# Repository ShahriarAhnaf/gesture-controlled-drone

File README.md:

# PalmPilot

Fly a drone with your hands. Two glove controllers, each an ESP32-S3 with five
flex sensors and a motion sensor, send their readings over Bluetooth to a third
ESP32-S3, the hub. The hub turns finger curl and hand tilt into stick commands for
ArduCopter. The controller is real hardware; the drone is simulated and flies on
screen.

## How it works

```text
left glove  ─┐
             ├─ BLE ─> hub ─ USB ─> laptop ─> ArduCopter ─> motor outputs ─> physics ─> 3D view
right glove ─┘          one command every 20 ms
```

The drone on screen moves only because ArduCopter's motor outputs moved it. No
gesture moves the drone directly.

On the laptop, ArduCopter runs as ArduPilot's native simulator (SITL) in real time.
The same firmware can also run on an emulated STM32F405 flight controller in the
[Simantic](https://simantic.com) simulator, which is how the automated tests fly it.

## Gestures

| Hand | Movement | Drone |
|---|---|---|
| Left | curl four fingers | throttle: open is zero, half curl holds height |
| Left | roll the hand | yaw |
| Right | tilt forward or back | pitch |
| Right | tilt left or right | roll |
| Left | press the button | ENABLE: commands only count while enabled |

Full table, deadbands and safety interlocks: [docs/gesture-mapping.md](docs/gesture-mapping.md).

## Hardware

Three ESP32-S3 DevKits, ten flex sensors and two Adafruit LSM6DS3TR-C + LIS3MDL
motion breakouts, on breadboards for now.

The [Rev B PCB design](hardware/README.md) replaces the DevKits with directly
soldered ESP32-S3-WROOM-1 modules on both hands and the hub. It includes KiCad
schematics, four-layer routing, fabrication review exports, passive simulation
evidence and Blender hand renders. The PCB revision still needs bench
qualification; the breadboard results above do not validate the new boards.

Parts: [docs/bom.md](docs/bom.md). Wiring for each board: [docs/wiring/](docs/wiring/README.md).

## Status

- The whole system works in simulation, from the gloves' firmware to the flying
  drone: both hands and the hub run their real firmware on simulated ESP32-S3s and
  fly ArduCopter on an emulated F405. The latest test run passed 321 of 322 checks.
- The physical controller is built on breadboards and has flown the simulated
  drone. One problem is open: a hand sometimes stops sending while it stays
  connected. Notes: [docs/bench-bringup.md](docs/bench-bringup.md).
- Not done yet: the physical test procedures, a soldered build, and pairing.

## Try it

Build the firmware (ESP-IDF v5.5.2):

```sh
idf.py -C firmware/apps/hand -D SDKCONFIG_DEFAULTS="sdkconfig.defaults;sdkconfig.left" build
idf.py -C firmware/apps/hub build
```

Fly the simulated drone with the keyboard, or with a physical hub (needs an
ArduPilot SITL build of Copter-4.7.1 in `tmp/ardupilot` and pymavlink):

```sh
python simulation/drone/demo_view.py --manual             # then open http://localhost:8765
python simulation/drone/demo_view.py --hub /dev/cu.usbserial-XXXX
```

The automated simulation tests (`firmware/tests/`) need the Simantic engine and
board files that are not public yet; [firmware/README.md](firmware/README.md)
describes them.

## How it was tested

Every feature was written and tested in simulation before any sensor was wired.
The simulator runs the exact images that are flashed onto the boards, with test
inputs entering through the simulated chip's own ADC, I2C and GPIO. The same images
then went onto the physical boards.

- [docs/simulation.md](docs/simulation.md): how the simulation runs, the tests, and how the physics was checked
- [docs/test-plan.md](docs/test-plan.md): every test, in order
- [docs/bench-bringup.md](docs/bench-bringup.md): moving to the physical boards, and what simulation could not catch
- [docs/demo.md](docs/demo.md): the laptop demo

## Repository layout

```text
firmware/apps/          hand and hub firmware (and a scripted stand-in hand for tests)
firmware/components/    logic shared by hand and hub: gesture mapping, interlocks, packet format
firmware/tests/         simulation test suites; run_all.sh runs them all
firmware/tools/         build and simulation wrappers; bench/ has tools for the physical boards
simulation/drone/       the bridge to ArduCopter, the physics model, the 3D view
docs/                   design, wiring, tests and notes
hardware/               Rev B module PCBs, electrical evidence and Blender assembly
```

Contributing: [CONTRIBUTING.md](CONTRIBUTING.md).

## Licence

MIT ([LICENSE](LICENSE)). `simulation/drone/ardupilot_frame.py` is a port of
ArduPilot code and is GPLv3; [NOTICE](NOTICE) lists it and the other exceptions.

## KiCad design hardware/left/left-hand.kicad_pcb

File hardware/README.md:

# PalmPilot Rev B — direct ESP32-S3-WROOM module boards

18 November 2026. Replaces the Rev A DevKit carriers at the canonical LEFT,
RIGHT and HUB KiCad paths. Rev A remains in git commit
`d93c8d5c258abfb121f0f205c3fb2d9bdec95d6e`. Rev B is an engineering
review on `hardware/wroom-module-revb`; no boards were ordered.

All three boards are **50 × 58 mm, four copper layers, 1.6 mm nominal**. Each
contains one **ESP32-S3-WROOM-1-N16R8 soldered directly to the PCB**, using its
built-in PCB antenna. There are no DevKit boards or module socket rows.
The 18 × 25.5 mm module overhangs the front edge by 6.25 mm. Its native keepout
contains no host copper. LEFT/RIGHT each retain five flex inputs and an external
Adafruit #5543 motion board. HUB includes its GPIO7 CALIBRATE circuit.

## Integrated support circuit

- TLV1117LV33DCYR ceramic-stable 1 A LDO converts USB 5 V to 3.3 V.
  22 uF / 25 V / X5R 1206 capacitors serve input, output and module bulk;
  local 100 nF capacitors bypass the module and bridge.
- CH340C operates at 3.3 V, with V3 tied to VCC and its internal oscillator.
  ESP GPIO43/TXD0 connects to bridge RXD; bridge TXD connects to GPIO44/RXD0.
  The hub retains UART0 / 115200 baud / JSON USB-to-laptop communication.
  Its R232 mode input is intentionally NC, using the manufacturer's internal pull-down.
- USB Micro-B J1 supplies power and programming/data; USBLC6-2SC6 protects D+/D−.
  The shield is grounded. Native ESP USB GPIO19/20 remain NC.
- EN uses 10 kR / 1 uF and RESET SW1. GPIO0 uses 10 kR and BOOT SW2.
  Hold BOOT, tap RESET, release BOOT to enter the ROM downloader.
  This revision uses manual flashing controls; it has no DTR/RTS auto-reset.
- No battery input or charger is fitted. Each hand uses a USB supply; HUB uses
  a USB data cable to the host. BLE connects the hands to the hub.

## Preserved interfaces and firmware

| Connector | Role | Pins |
|---|---|---|
| J4/J5/J6/J7/J8 | Thumb/index/middle/ring/little flex | 1 = 3V3, 2 = ADC; GPIO1/2/4/5/6 |
| J2, hands only | External #5543 motion harness | 1 GND, 2 3V3, 3 SDA/GPIO8, 4 SCL/GPIO9 |
| J9, LEFT only | Normally-open ENABLE switch | 1 switch, 2 GND; GPIO7 conditioning |
| SW3, HUB only | CALIBRATE | GPIO7 through 10 kR / 100 nF / 1 kR network |

The PH-4 harness is not a QT-compatible cable; verify its mapping. Each flex
input retains 47 kR 1% / 100 nF to ground. The breakout supplies I2C pull-ups;
none are added here. GPIO10, GPIO3/45/46 strapping pins, unused native USB and
module GPIO35/36/37 associated with octal PSRAM remain NC. RIGHT GPIO7 is NC.
The upstream firmware was not modified or rebuilt in this revision. Its existing
8 MB flash image fits the selected 16 MB flash module; PSRAM remains disabled.
A physical boot/flash/USB/BLE/ADC/IMU test is still required, including module
variant and firmware configuration. HUB bench mode disables CALIBRATE.

## Checks and limits

All three saved projects pass KiCad 10.0.3 ERC, DRC with schematic parity, and a
read-only native pad-connectivity audit: **zero reported violations or opens**.
Tracks follow H/V/45 geometry. Reports, board hashes, BOMs, four-layer Gerbers,
drills, layer plots, schematic PDFs and component-bearing GLBs are in `build/`.
All twelve copper Gerber layers were also rendered with PyGerber 2.4.3 at
500 dpi and visually inspected; In1 remains a continuous reference plane.
The project-local WROOM footprint retains the native land pattern, thermal vias,
RF keepout and STEP model; only off-board silkscreen was removed.

In1.Cu is a continuous ground reference; In2.Cu carries 3V3 and a few slow signals
and the USB 5 V feed. Top and bottom have ground pours and stitching. Exact
fabricator stackup, USB differential impedance and signal quality are **not
qualified**. The short full-speed USB route includes a crossover via pair on D+
with nearby return stitching; it is not a length-matched or impedance-certified
USB release. Confirm the Molex connector mechanical drawing and mating clearance
before manufacture; its exact installed-library 3D model is unavailable.

[Simulation results](simulation/REPORT.md) bind to the actual new netlists.
Passive response, EN timing and assumed rail impedance were simulated; the LDO
control loop, radio current waveform, antenna/body interaction, sensor silicon
and raw ADC transfer were not. At 5.25 V / 0.5 A the LDO dissipates about 0.975 W:
actual sustained-load and worn temperatures must be measured. I2C capacitance
and firmware raw fault thresholds remain bench qualifications.

BOMs contain selected module, active-component and capacitor MPNs. Resistor,
connector and switch procurement variants are not frozen; BOMs and Gerbers are
engineering review outputs, not an assembly order or fabrication release.

## Render and rebuilding

`render/palmpilot-two-hands.blend` contains both licensed real hand meshes, the
actual three module-board GLBs, ten sensor films and an illustrative harness.
`render/module-on-hand.png` shows the left module closely;
`render/right-hand-detail.png` and `render/hub-detail.png` show the other two. There is no added
DevKit or module proxy. The missing USB connector shell, external IMU envelopes,
straps, cushions, screws, sensor films and cables are illustrative; this does not
establish wearable fit. See [render notes](render/README.md).

Use KiCad's bundled Python for `scripts/generate.py`, then `scripts/export.py`,
`scripts/audit.py` and `simulation/run.py`. Use Blender for `render/scene.py` after
exporting all three GLBs; `render/details.py` adds the right-hand and hub close-ups.
Native GUI initialization may need an unsandboxed macOS
process. Export fails closed on ERC/DRC violations.

## Manufacturer references

- [Espressif module datasheet](https://www.espressif.com/sites/default/files/documentation/esp32-s3-wroom-1_wroom-1u_datasheet_en.pdf)
- [Espressif schematic checklist](https://docs.espressif.com/projects/esp-hardware-design-guidelines/en/latest/esp32s3/schematic-checklist.html)
- [Espressif layout guidance](https://docs.espressif.com/projects/esp-hardware-design-guidelines/en/latest/esp32s3/pcb-layout-design.html)
- [TI TLV1117LV](https://www.ti.com/lit/ds/symlink/tlv1117lv.pdf)
- [WCH CH340 manual](https://www.wch-ic.com/downloads/CH340DS1_PDF.html)
- [ST USBLC6-2](https://www.st.com/resource/en/datasheet/usblc6-2.pdf)
- [Molex USB connector](https://www.molex.com/en-us/products/part-detail/1050170001)

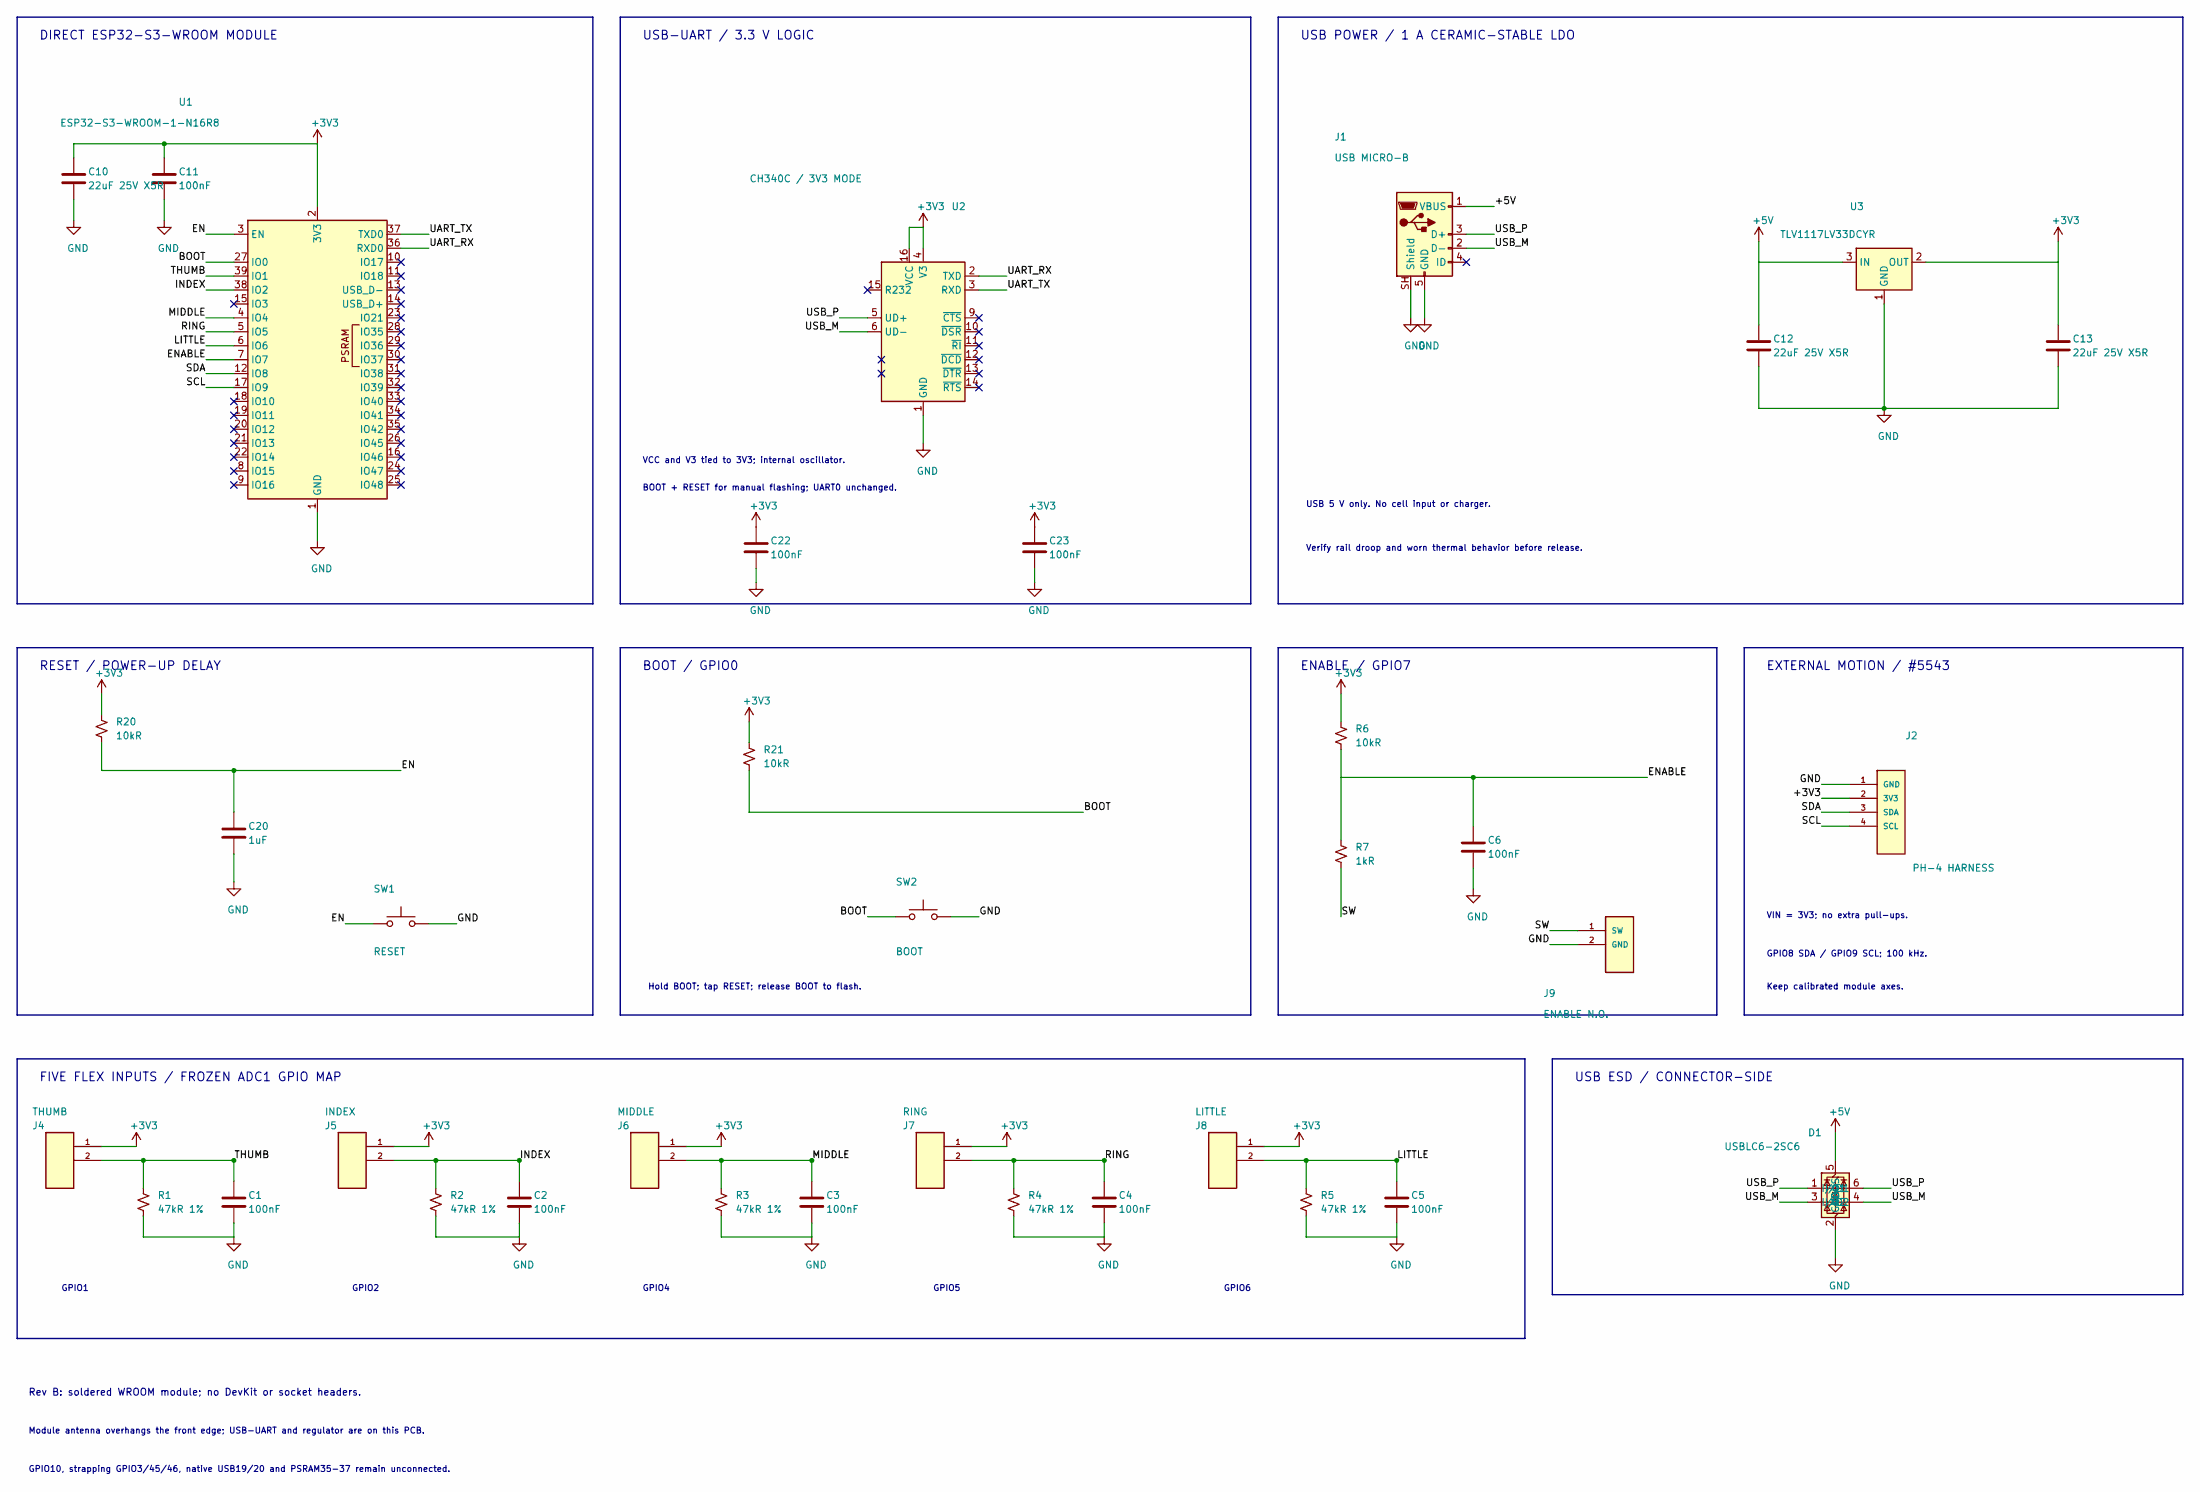
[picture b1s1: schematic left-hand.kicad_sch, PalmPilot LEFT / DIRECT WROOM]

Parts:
C1, C2, C3, C4, C5, C6, C11, C22, C23: 100nF; C_0805_2012Metric; MPN CC0805KRX7R9BB104; LCSC C49678
C10, C12, C13: 22uF 25V X5R; C_1206_3216Metric; MPN CL31A226KAHNNNE; LCSC C12891
C20: 1uF; C_0805_2012Metric; MPN CL21B105KBFNNNE; LCSC C28323
D1: USBLC6-2SC6; SOT-23-6; MPN USBLC6-2SC6; LCSC C7519
J1: USB MICRO-B; USB_Micro-B_Molex-105017-0001; MPN 1050170001; LCSC C136000
J2: PH-4 HARNESS; JST_PH_B4B-PH-K_1x04_P2.00mm_Vertical
J4: THUMB; JST_PH_B2B-PH-K_1x02_P2.00mm_Vertical
J5: INDEX; JST_PH_B2B-PH-K_1x02_P2.00mm_Vertical
J6: MIDDLE; JST_PH_B2B-PH-K_1x02_P2.00mm_Vertical
J7: RING; JST_PH_B2B-PH-K_1x02_P2.00mm_Vertical
J8: LITTLE; JST_PH_B2B-PH-K_1x02_P2.00mm_Vertical
J9: ENABLE N.O.; JST_PH_B2B-PH-K_1x02_P2.00mm_Vertical
R1, R2, R3, R4, R5: 47kR 1%; R_0805_2012Metric
R6, R20, R21: 10kR; R_0805_2012Metric
R7: 1kR; R_0805_2012Metric
SW1: RESET; SW_PUSH_6mm
SW2: BOOT; SW_PUSH_6mm
U1: ESP32-S3-WROOM-1-N16R8; ESP32-S3-WROOM-1; MPN ESP32-S3-WROOM-1-N16R8; LCSC C2913202
U2: CH340C / 3V3 MODE; SOIC-16_3.9x9.9mm_P1.27mm; MPN CH340C; LCSC C84681
U3: TLV1117LV33DCYR; SOT-223-3_TabPin2; MPN TLV1117LV33DCYR; LCSC C15578

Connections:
+3V3: C10.1, C11.1, C13.1, C22.1, C23.1, J2.2 (3V3), J4.1, J5.1, J6.1, J7.1, J8.1, R6.1, R20.1, R21.1, U1.2 (3V3), U2.4 (V3), U2.16 (VCC), U3.2 (OUT)
+5V: C12.1, D1.5 (VBUS), J1.1 (VBUS), U3.3 (IN)
/BOOT: R21.2, SW2.1, U1.27 (IO0)
/EN: C20.1, R20.2, SW1.1, U1.3 (EN)
/ENABLE: C6.1, R6.2, R7.1, U1.7 (IO7)
/INDEX: C2.1, J5.2, R2.1, U1.38 (IO2)
/LITTLE: C5.1, J8.2, R5.1, U1.6 (IO6)
/MIDDLE: C3.1, J6.2, R3.1, U1.4 (IO4)
/RING: C4.1, J7.2, R4.1, U1.5 (IO5)
/SCL: J2.4 (SCL), U1.17 (IO9)
/SDA: J2.3 (SDA), U1.12 (IO8)
/SW: J9.1 (SW), R7.2
/THUMB: C1.1, J4.2, R1.1, U1.39 (IO1)
/UART_RX: U1.36 (RXD0), U2.2 (TXD)
/UART_TX: U1.37 (TXD0), U2.3 (RXD)
/USB_M: D1.3 (I/O2), D1.4 (I/O2), J1.2 (D-), U2.6 (UD-)
/USB_P: D1.1 (I/O1), D1.6 (I/O1), J1.3 (D+), U2.5 (UD+)
GND: C1.2, C2.2, C3.2, C4.2, C5.2, C6.2, C10.2, C11.2, C12.2, C13.2, C20.2, C22.2, C23.2, D1.2 (GND), J1.5 (GND), J1.SH (Shield), J2.1 (GND), J9.2 (GND), R1.2, R2.2, R3.2, R4.2, R5.2, SW1.2, SW2.2, U1.1 (GND), U1.40 (GND), U1.41 (GND), U2.1 (GND), U3.1 (GND)

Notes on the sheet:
DIRECT ESP32-S3-WROOM MODULE
USB-UART / 3.3 V LOGIC
VCC and V3 tied to 3V3; internal oscillator.
BOOT + RESET for manual flashing; UART0 unchanged.
USB POWER / 1 A CERAMIC-STABLE LDO
USB 5 V only. No cell input or charger.
Verify rail droop and worn thermal behavior before release.
RESET / POWER-UP DELAY
BOOT / GPIO0
Hold BOOT; tap RESET; release BOOT to flash.
ENABLE / GPIO7
EXTERNAL MOTION / #5543
VIN = 3V3; no extra pull-ups.
GPIO8 SDA / GPIO9 SCL; 100 kHz.
Keep calibrated module axes.
FIVE FLEX INPUTS / FROZEN ADC1 GPIO MAP
GPIO1
GPIO2
GPIO4
GPIO5
GPIO6
USB ESD / CONNECTOR-SIDE
Rev B: soldered WROOM module; no DevKit or socket headers.
Module antenna overhangs the front edge; USB-UART and regulator are on this PCB.
GPIO10, strapping GPIO3/45/46, native USB19/20 and PSRAM35-37 remain unconnected.

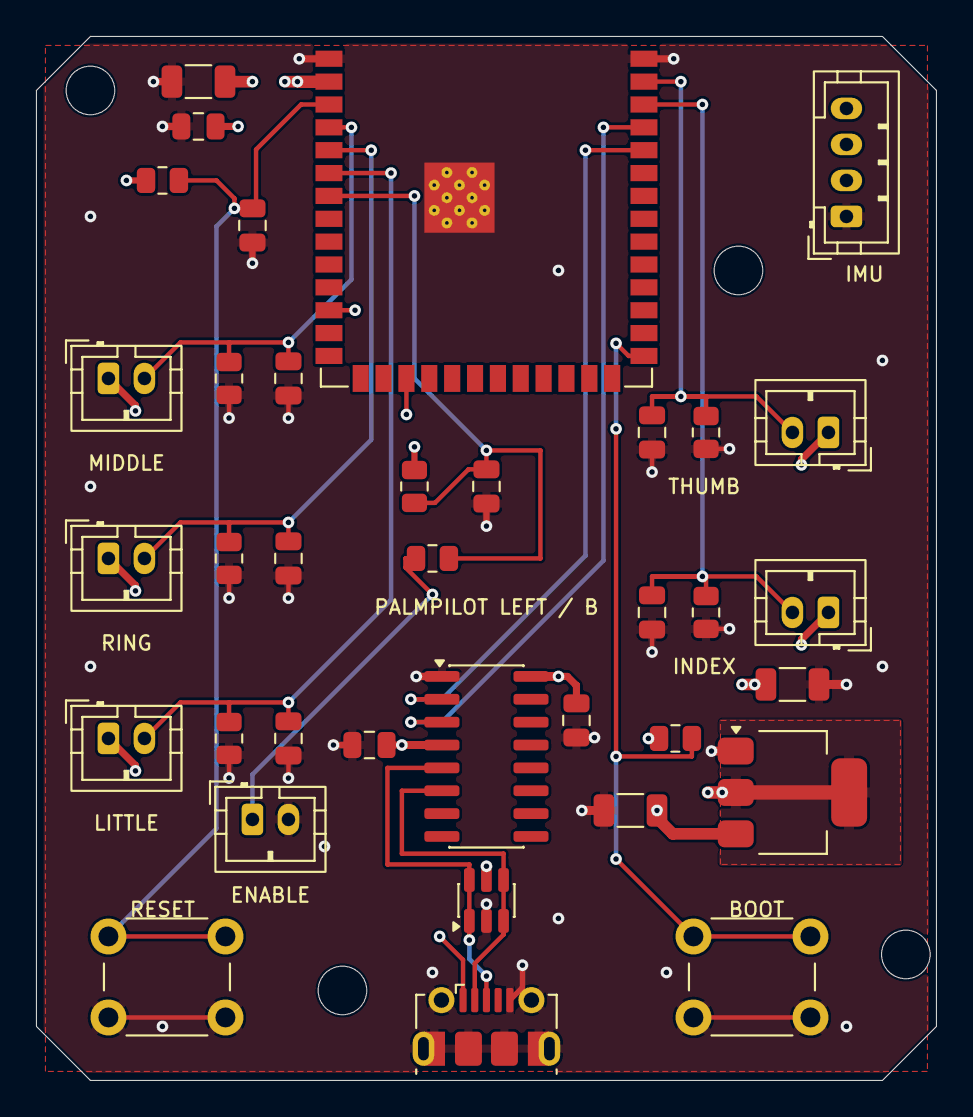
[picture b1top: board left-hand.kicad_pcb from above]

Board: 4 copper layers, 50.0 x 58.0 mm, 40 parts (0 on the bottom side), 18 nets.

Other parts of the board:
H1, H2, H3, H4: MountingHole_2.7mm_M2.5

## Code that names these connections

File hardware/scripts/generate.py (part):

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  sym('PalmPilot:IMU','J2','PH-4 HARNESS',352,157,JST4,{'1':'GND','2':'+3V3','3':'SDA','4':'SCL'},[(354,146),(355,170)]);expose('J2')
  text('VIN = 3V3; no extra pull-ups.',329,179,1.1);text('GPIO8 SDA / GPIO9 SCL; 100 kHz.',329,186,1.1);text('Keep calibrated module axes.',329,192,1.1)
  rect(10,205,275,51,'FIVE FLEX INPUTS / FROZEN ADC1 GPIO MAP')
  for i,(net,gpio) in enumerate(zip(['THUMB','INDEX','MIDDLE','RING','LITTLE'],[1,2,4,5,6]),1):
   x=18+(i-1)*53;y=223;jn='J'+str(i+3)
   sym('PalmPilot:Flex',jn,net,x,y,JST2,{'1':'+3V3','2':net},[(x-5,y-6),(x-5,y-9)])
   w((x+7.62,y-2.54),(x+14,y-2.54));power('+3V3',x+14,y-2.54);w((x+7.62,y),(x+31,y));label(net,x+31,y)
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 supply('C22',2,(31,38.95),'GND',.35);supply('U2',1,(21.1,35.555),'GND',.4)
 supply('U2',4,(20.3,39.365),width=.4);path('+3V3',[pp('U2',4),pp('C23',1)],width=.4);supply('C23',2,(16.5,39.365),'GND',.35)
 # UART0: ESP TX -> bridge RX; bridge TX -> ESP RX. All slow routes reference In1 GND.
 for net,pin,x,cy,chip in [('UART_TX',37,31.5,29.12,3),('UART_RX',36,30.5,28.85,2)]:
  yy=pp('U1',pin)[1];path(net,[pp('U1',pin),(x,yy)]);via(net,x,yy);end=(20.8,pp('U2',chip)[1]);path(net,[(x,yy),(x,cy),end],p.B_Cu);via(net,*end);path(net,[end,pp('U2',chip)])
 # Reset/boot: 10k / 1uF EN delay and physical manual-flash buttons.
 supply('R20',1,(5,8),width=.35)
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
